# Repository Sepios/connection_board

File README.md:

connection_board
================

The KiCad files (schemes, layouts, gerbers) for the Sepios connection board.

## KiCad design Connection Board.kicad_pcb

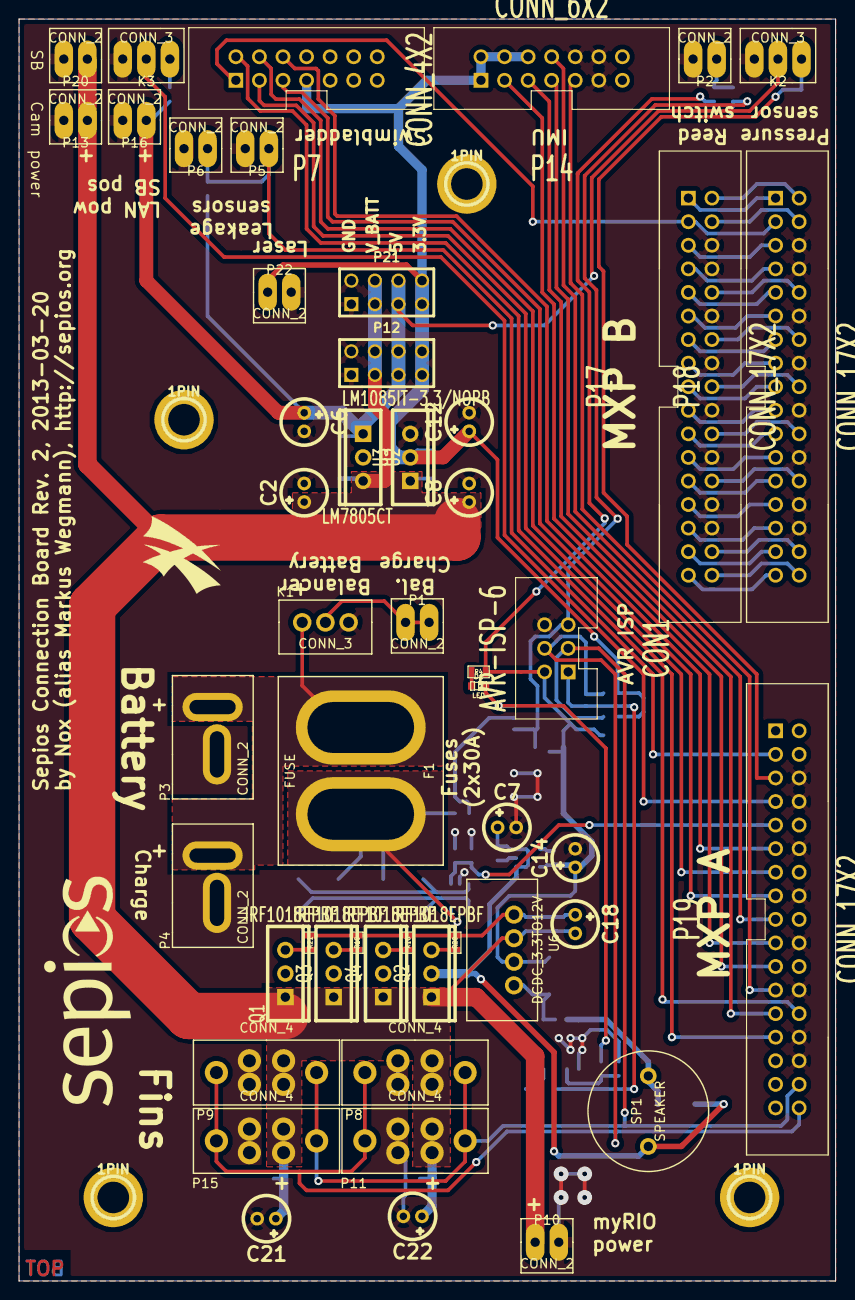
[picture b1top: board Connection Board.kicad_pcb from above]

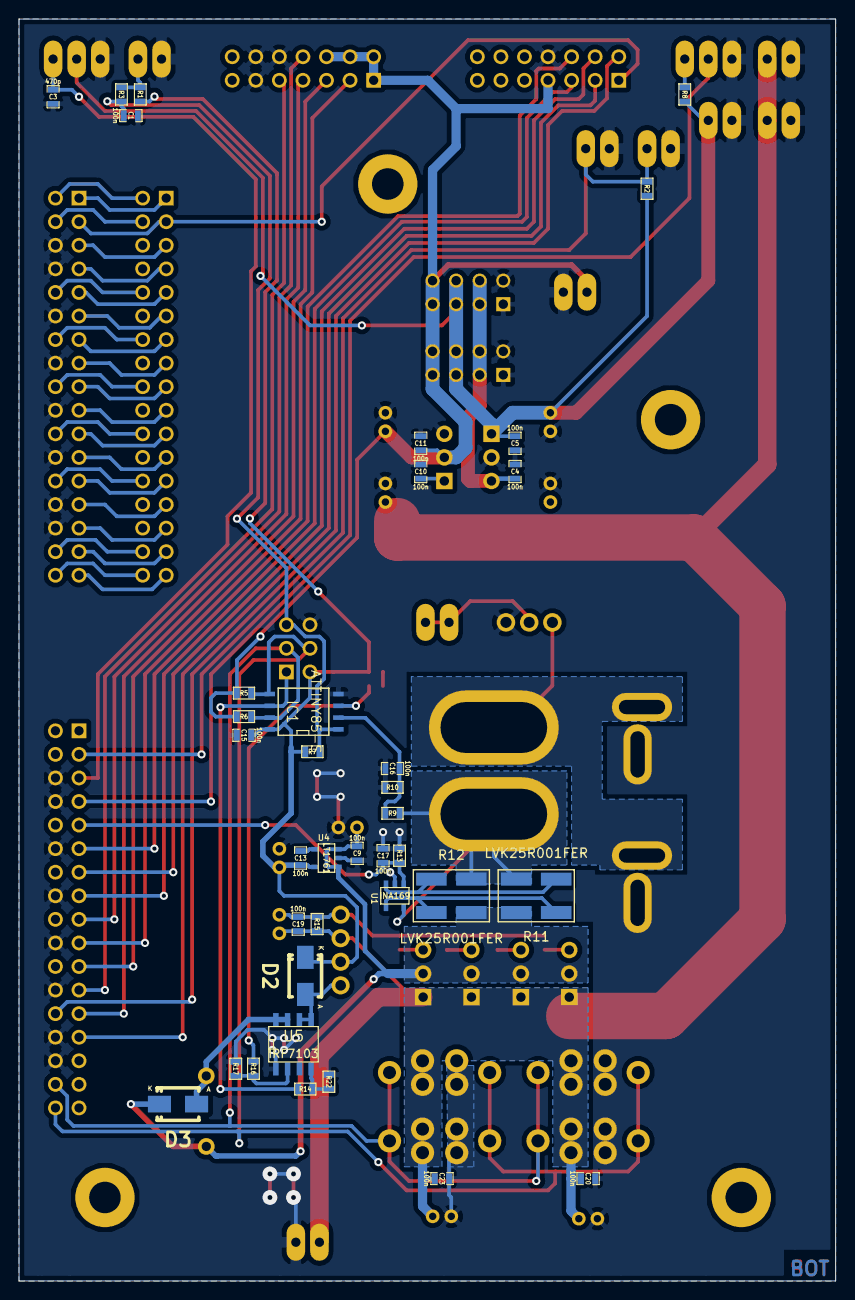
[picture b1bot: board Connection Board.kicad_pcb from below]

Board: 2 copper layers, 88.0 x 136.0 mm, 93 parts (37 on the bottom side), 70 nets.

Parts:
1PIN, 1PIN#2, 1PIN#3, 1PIN#4: P***; 1pin
C1, C4, C5, C9, C10, C11, C13, C15, C16, C17, C19, C20, C23: 100n; SM0603_Capa
C2, C7, C8, C14, C21, C22: 47u; Elko_vert_DM5_RM2_WITHOUT_CU_INDICATOR
C3: 470p; SM0603_Capa
C6, C12: 22u; Elko_vert_DM5_RM2_WITHOUT_CU_INDICATOR
C18: 4.7u; Elko_vert_DM5_RM2_WITHOUT_CU_INDICATOR
CON1: AVR-ISP-6; PinArray_2x3_tub
D1: LED; LED-0603
D2, D3: DIODE; Diode-SMA_Standard_RevA_26July2010
F1: FUSE; FUSE_BLADE
IC1: ATTINY85-S; SO8W
K1: CONN_3; XH3_PLUG
K2, K3: CONN_3; PRINT_3
P1, P2, P5, P6, P10, P13, P16, P20, P22: CONN_2; PRINT_2
P3, P4: CONN_2; T_PLUG
P7: CONN_4X2; PinArray_2x7_tub
P8, P9, P11, P15: CONN_4; FIN_CONNECTOR
P12, P21: CONN_4X2; pin_array_4x2
P14: CONN_6X2; PinArray_2x7_tub
P17, P18, P19: CONN_17X2; PinArray_2x17_tub
Q1, Q2, Q3, Q4: IRF1018EPBF; TO220_VERT_123
R1, R22: 10k; SM0603
R2: 220k; SM0603
R3, R4, R14, R16: 22; SM0603
R5, R6, R15: 4.7k; SM0603
R7: 47k; SM0603
R8: 0; SM0603
R9, R17: 100k; SM0603
R10: 22k; SM0603
R11, R12: LVK25R001FER
R13: 82k; SM0603
R18, R19, R20, R21: 10; SM0603
SP1: SPEAKER; CPM121
U1: INA169; SOT23-5
U2: LM7805CT; TO220_VERT_123
U3: LM1085IT-3.3/NOPB; TO220_VERT_123
U4: LT1761; SOT23-5
U5: IRF7103; SO8E
U6: DCDC_3.3TO12V; MEE1S0505SC
VAL: sepios_logo
VAL#2: nox_logo

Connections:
+3.3V: C11.1, C12.1, P7.7, P12.7, P12.8, P14.1, P14.2, P14.4, P14.6, P21.7, P21.8, P22.2, R5.1, R6.1, U3.2
+5V: C5.1, C6.1, K2.2, P12.5, P12.6, P16.2, P21.5, P21.6, R2.2, R8.1, U2.3
+BATT: F1.1, K1.3, P3.2, P4.2
+V: C7.1, C9.1, D3.2, Q1.2, Q2.2, Q3.2, Q4.2, R11.1, R12.2, SP1.1, U4.1, U4.3
/BAL: K1.2, P1.1, P1.2
/CUR_SENSE: C17.1, P19.9, R13.1, U1.1
/DBG_LED: D1.2, IC1.3, R16.1
/IMU_/CS: P14.3, P19.19
/IMU_IRQ: P14.8, P19.17
/LEAK_SENSOR: P5.2, P6.2, P19.3, R2.1
/MISO: P14.9, P19.23
/MOSI: P14.7, P19.25
/PRESSURE_SENSOR: C3.1, K2.3, P19.5
/REED: C1.1, CON1.5, IC1.1, R3.2, R7.1
/SB_/SF: P7.2, P19.26
/SB_EN: P7.6, P19.11
/SB_FB: P7.1, P17.3, P18.3
/SB_IN1: P7.4, P19.13
/SB_IN2: P7.5, P19.15
/SB_POS: K3.2, P19.7
/SB_PWM: P7.3, P19.27
/SCL: CON1.3, IC1.7, P8.3, P9.3, P11.3, P15.3, P19.32, R6.2
/SCLK: P14.5, P19.21
/SDA: CON1.4, IC1.5, P8.4, P9.4, P11.4, P15.4, P19.34, R5.2
/SYS_EN: CON1.1, IC1.6, R14.1
/VOLT_SENSE: C16.1, IC1.2, R9.2, R10.1
GND: C1.2, C2.2, C3.2, C4.2, C5.2, C6.2, C7.2, C8.2, C9.2, C10.2, C11.2, C12.2, C14.2, C15.2, C16.2, C17.2, C20.2, C21.2, C22.2, C23.2, CON1.6, IC1.4, K1.1, K2.1, K3.1, P2.1, P3.1, P4.1, P5.1, P6.1, P7.8, P8.1, P9.1, P10.1, P11.1, P12.1, P12.2, P13.1, P14.10, P14.11, P14.12, P15.1, P16.1, P17.6, P17.8, P17.12, P17.16, P17.20, P17.24, P17.28, P17.30, P18.6, P18.8, P18.12, P18.16, P18.20, P18.24, P18.28, P18.30, P19.6, P19.8, P19.12, P19.16, P19.20, P19.24, P19.28, P19.30, P20.1, P21.1, P21.2, P22.1, R10.2, R13.2, R17.2, R22.2, U1.2, U2.2, U3.1, U4.2, U5.1, U5.3
unnamed: F1.2, R9.1, R11.2, R12.1, U1.5
unnamed: R11.4, R12.3, U1.3
unnamed: R11.3, R12.4, U1.4
unnamed: D2.1, U5.5, U5.6, U6.1
unnamed: P17.18, P18.18
unnamed: R14.2, R22.1, U5.4
unnamed: D3.1, SP1.2, U5.7, U5.8
unnamed: R16.2, R17.1, U5.2
unnamed: Q2.1, R20.2
unnamed: Q4.1, R18.2
unnamed: Q1.1, R21.2
unnamed: Q3.1, R19.2
unnamed: C18.1, C19.1, R15.1, R18.1, R19.1, R20.1, R21.1, U6.4
unnamed: P17.32, P18.32
unnamed: P17.34, P18.34
unnamed: P17.14, P18.14
unnamed: P17.10, P18.10
unnamed: P17.22, P18.22
unnamed: P17.26, P18.26
unnamed: P17.4, P18.4
unnamed: P17.2, P18.2
unnamed: P17.29, P18.29
unnamed: P17.33, P18.33
unnamed: P17.15, P18.15
unnamed: P17.25, P18.25
unnamed: P17.17, P18.17
unnamed: P17.27, P18.27
unnamed: P17.19, P18.19
unnamed: P17.23, P18.23
unnamed: P17.7, P18.7
unnamed: D1.1, R4.2
unnamed: P17.1, P18.1
unnamed: P17.5, P18.5
unnamed: P17.9, P18.9
unnamed: P17.11, P18.11
unnamed: P17.21, P18.21
unnamed: P17.31, P18.31
unnamed: P17.13, P18.13
unnamed: C13.2, U4.4
unnamed: P2.2, R1.1, R3.1
unnamed: K3.3, R8.2
VCC: C13.1, C14.1, C15.1, CON1.2, D2.2, IC1.8, R1.2, R4.1, R7.2, U4.5, U6.2
V_SYS: C2.1, C4.1, C8.1, C10.1, C18.2, C19.2, C20.1, C21.1, C22.1, C23.1, P8.2, P9.2, P10.2, P11.2, P12.3, P12.4, P13.2, P15.2, P20.2, P21.3, P21.4, Q1.3, Q2.3, Q3.3, Q4.3, R15.2, U2.1, U3.3, U6.3

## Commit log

2014-06-13 Add KiCad project
2014-06-14 Add PDF
